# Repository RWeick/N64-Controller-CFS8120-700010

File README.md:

# N64-Controller-CFS8120-700010
The Kicad files for a variant of the N64 Controller PCB

PCB Thickness: 1.6 mm

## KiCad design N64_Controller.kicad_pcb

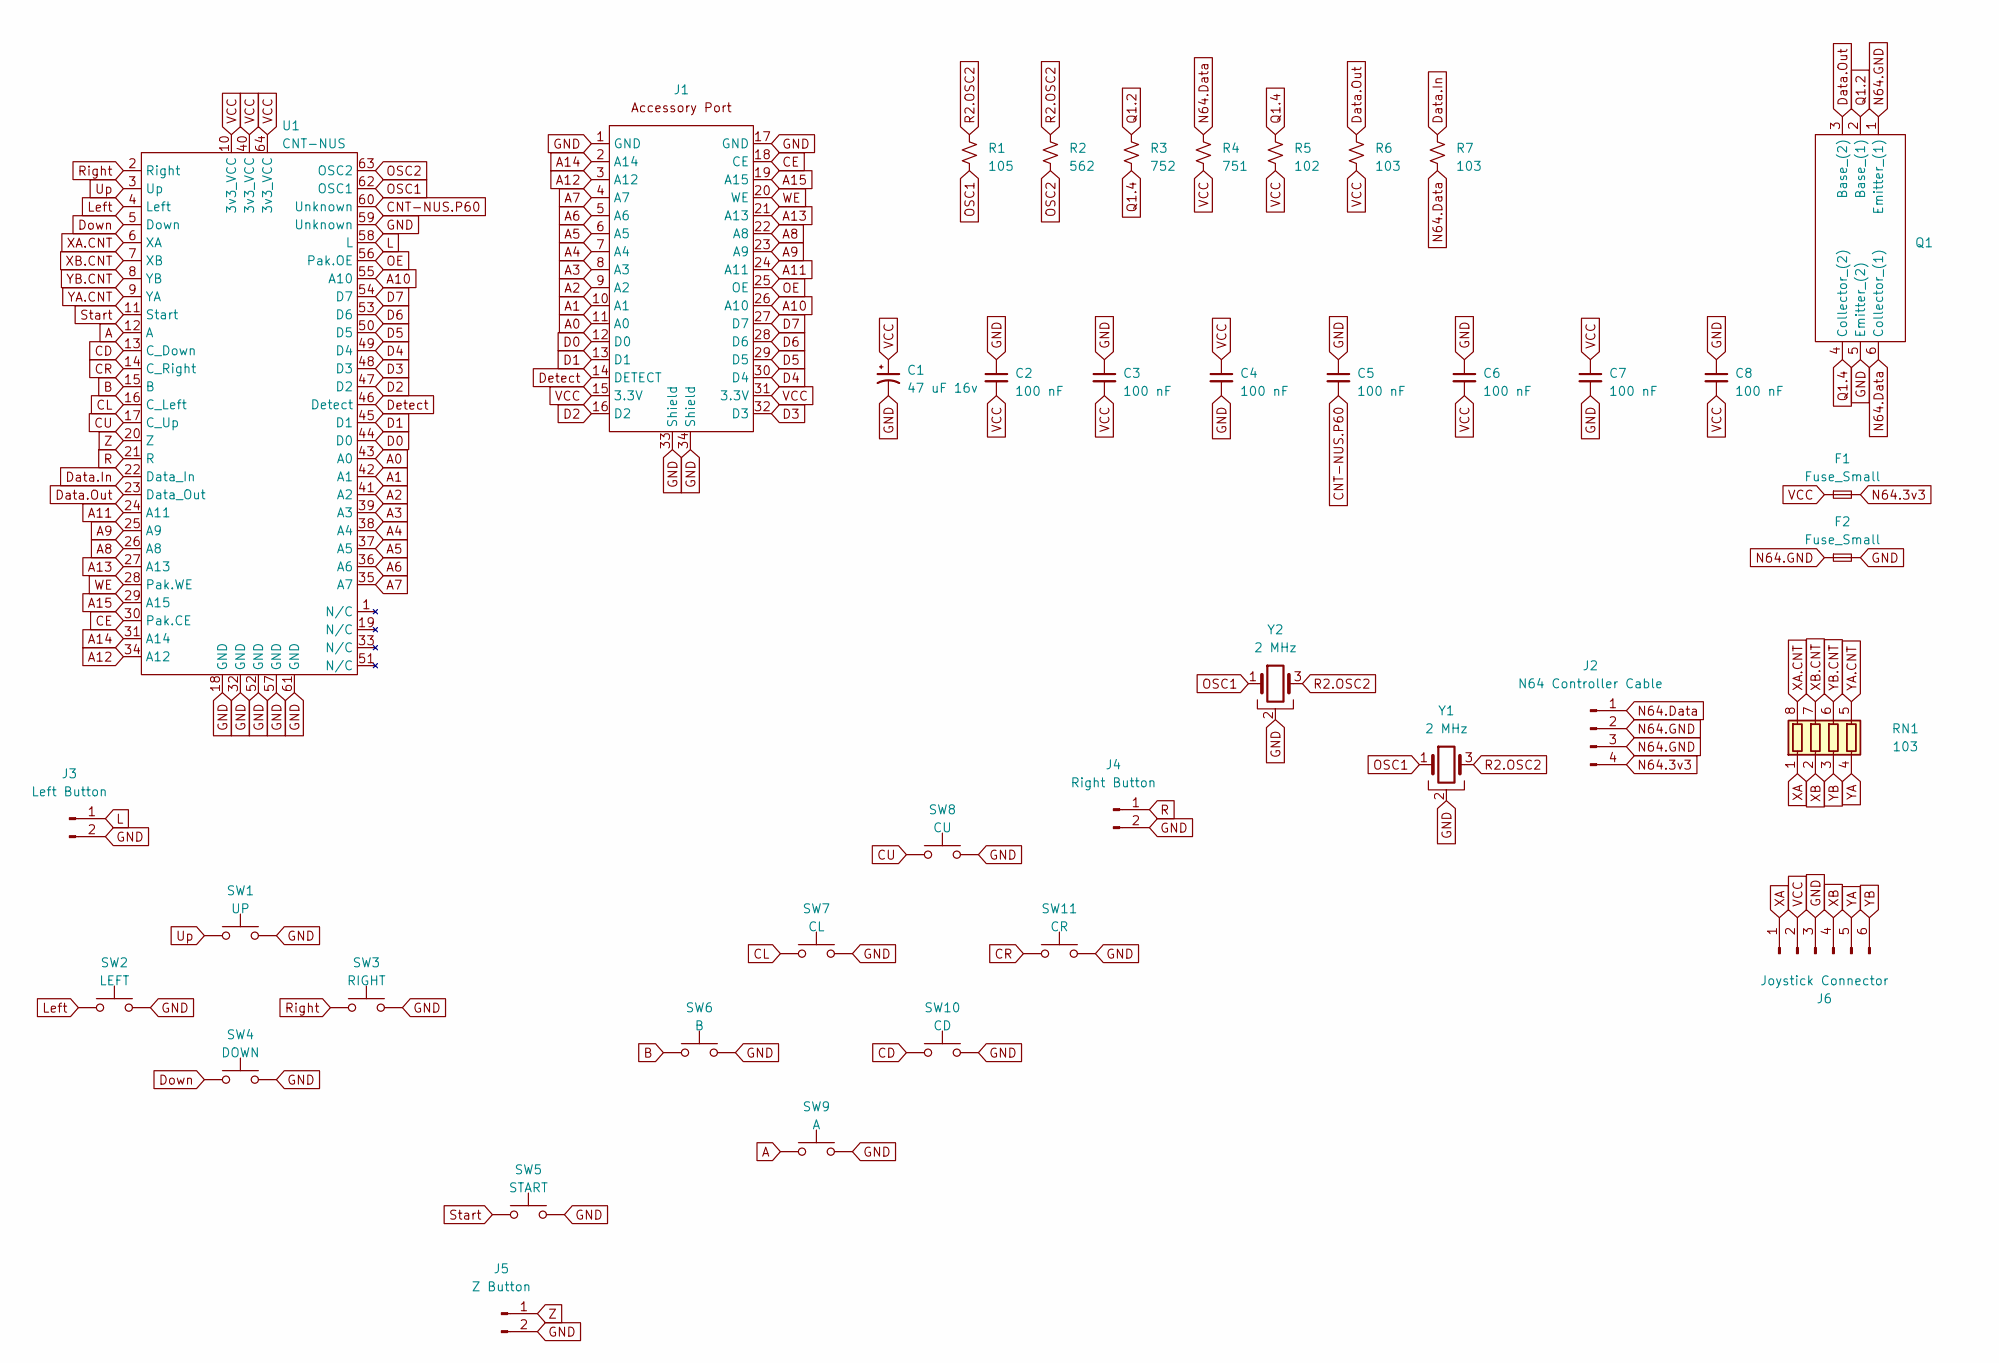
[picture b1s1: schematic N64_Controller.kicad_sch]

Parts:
C1: 47 uF 16v; CP_Radial_D5.0mm_P2.50mm
C2, C3, C4, C5, C6, C7, C8: 100 nF; Small SMD
F1, F2: Fuse_Small; Small SMD
J1: Accessory Port
J2: N64 Controller Cable; N64 Plug Cable Connector
J3: Left Button; Button Board Connector
J4: Right Button; Button Board Connector
J5: Z Button; Button Board Connector
J6: Joystick Connector
Q1: HE Diode
R1: 105; Large SMD
R2: 562; Large SMD
R3: 752; Small SMD
R4: 751; Small SMD
R5: 102; Small SMD
R6, R7: 103; Small SMD
RN1: 103; Resistor Array
SW1: UP; D-Pad Button
SW2: LEFT; D-Pad Button
SW3: RIGHT; D-Pad Button
SW4: DOWN; D-Pad Button
SW5: START; Start Button
SW6: B; B Button
SW7: CL; CL Button
SW8: CU; CU Button
SW9: A; A Button
SW10: CD; CD Button
SW11: CR; CR Button
U1: CNT-NUS
Y1: 2 MHz; 2 MHz Oscillator
Y2: 2 MHz; 2 Mhz Oscillator SMD

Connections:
A: SW9.1, U1.12 (A)
A0: J1.11 (A0), U1.43 (A0)
A1: J1.10 (A1), U1.42 (A1)
A2: J1.9 (A2), U1.41 (A2)
A3: J1.8 (A3), U1.39 (A3)
A4: J1.7 (A4), U1.38 (A4)
A5: J1.6 (A5), U1.37 (A5)
A6: J1.5 (A6), U1.36 (A6)
A7: J1.4 (A7), U1.35 (A7)
A8: J1.22 (A8), U1.26 (A8)
A9: J1.23 (A9), U1.25 (A9)
A10: J1.26 (A10), U1.55 (A10)
A11: J1.24 (A11), U1.24 (A11)
A12: J1.3 (A12), U1.34 (A12)
A13: J1.21 (A13), U1.27 (A13)
A14: J1.2 (A14), U1.31 (A14)
A15: J1.19 (A15), U1.29 (A15)
B: SW6.1, U1.15 (B)
CD: SW10.1, U1.13 (C_Down)
CE: J1.18 (CE), U1.30 (Pak.CE)
CL: SW7.1, U1.16 (C_Left)
CNT-NUS.P60: C5.2, U1.60 (Unknown)
CR: SW11.1, U1.14 (C_Right)
CU: SW8.1, U1.17 (C_Up)
D0: J1.12 (D0), U1.44 (D0)
D1: J1.13 (D1), U1.45 (D1)
D2: J1.16 (D2), U1.47 (D2)
D3: J1.32 (D3), U1.48 (D3)
D4: J1.30 (D4), U1.49 (D4)
D5: J1.29 (D5), U1.50 (D5)
D6: J1.28 (D6), U1.53 (D6)
D7: J1.27 (D7), U1.54 (D7)
Data.22: R7.1, U1.22 (Data)
Data.23: Q1.3 (Base_(2)), R6.1, U1.23 (Data)
Detect: J1.14 (DETECT), U1.46 (Detect)
Down: SW4.1, U1.5 (Down)
GND: C1.2, C2.1, C3.1, C4.2, C5.1, C6.1, C7.2, C8.1, F2.2, J1.1 (GND), J1.17 (GND), J1.33 (Shield), J1.34 (Shield), J3.2, J4.2, J5.2, J6.3, Q1.5 (Emitter_(2)), SW1.2, SW2.2, SW3.2, SW4.2, SW5.2, SW6.2, SW7.2, SW8.2, SW9.2, SW10.2, SW11.2, U1.18 (GND), U1.32 (GND), U1.52 (GND), U1.57 (GND), U1.59 (Unknown), U1.61 (GND), Y1.2, Y2.2
L: J3.1, U1.58 (L)
Left: SW2.1, U1.4 (Left)
N64.3v3: F1.2, J2.4
N64.Data: J2.1, Q1.6 (Collector_(1)), R4.1, R7.2
N64.GND: F2.1, J2.2, J2.3, Q1.1 (GND)
OE: J1.25 (OE), U1.56 (Pak.OE)
OSC1: R1.2, U1.62 (OSC1), Y1.1, Y2.1
OSC2: R2.2, U1.63 (OSC2)
Q1.2: Q1.2 (Base_(1)), R3.1
Q1.4: Q1.4 (Collector_(2)), R3.2, R5.1
R: J4.1, U1.21 (R)
R2.OSC2: R1.1, R2.1, Y1.3, Y2.3
Right: SW3.1, U1.2 (Right)
Start: SW5.1, U1.11 (Start)
Up: SW1.1, U1.3 (Up)
VCC: C1.1, C2.2, C3.2, C4.1, C6.2, C7.1, C8.2, F1.1, J1.15 (3.3V), J1.31 (3.3V), J6.2, R4.2, R5.2, R6.2, U1.10 (3v3_VCC), U1.40 (3v3_VCC), U1.64 (3v3_VCC)
WE: J1.20 (WE), U1.28 (Pak.WE)
XA: J6.1, RN1.1 (R1.1)
XA.CNT: RN1.8 (R1.2), U1.6 (XA)
XB: J6.4, RN1.2 (R2.1)
XB.CNT: RN1.7 (R2.2), U1.7 (XB)
YA: J6.5, RN1.4 (R4.1)
YA.CNT: RN1.5 (R4.2), U1.9 (YA)
YB: J6.6, RN1.3 (R3.1)
YB.CNT: RN1.6 (R3.2), U1.8 (YB)
Z: J5.1, U1.20 (Z)

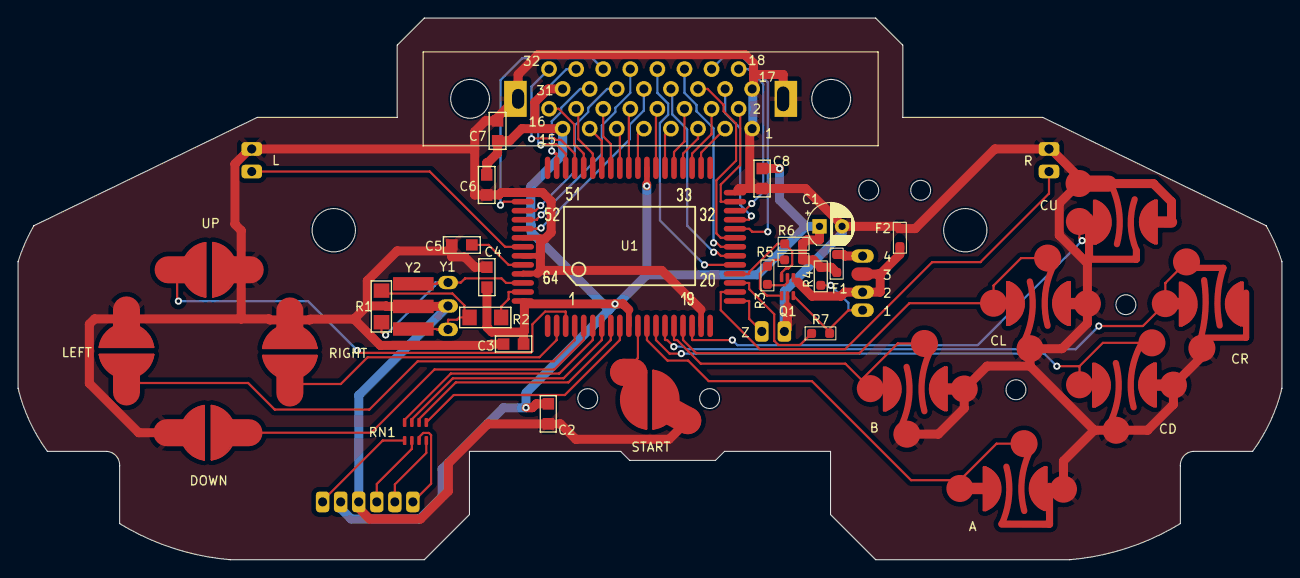
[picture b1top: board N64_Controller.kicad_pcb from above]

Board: 2 copper layers, 140.0 x 60.0 mm, 47 parts (0 on the bottom side), 63 nets.

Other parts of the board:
H1, H6: MountingHole_4.5mm
H2, H3, H4, H5, H7, H8: MountingHole_2.2mm_M2
